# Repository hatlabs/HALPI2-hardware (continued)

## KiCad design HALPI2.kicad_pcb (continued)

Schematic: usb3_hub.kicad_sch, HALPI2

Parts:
C82, C83, C92, C93, C94, C95, C96, C97, C98, C99, C100, C102, C103, C104, C105, C106, C107, C108, C109, C110, C112: 100nF; C_0201_0603Metric; LCSC C76934
C84, C90, C91: 4.7uF; C_0603_1608Metric; LCSC C19666
C85: 22uF; C_1206_3216Metric; LCSC C12891
C86, C111: 10uF; C_0805_2012Metric; LCSC C15850
C87, C88: 12pF; C_0402_1005Metric; LCSC C1547
C89, C101, C113, C114, C115, C116, C117, C118, C119, C120: 1uF; C_0402_1005Metric; LCSC C52923
D23: 1N4148WT; D_SOD-523; LCSC C7420320
FB4: BLM21PG600SN1; L_0805_2012Metric; LCSC C18305
L5: 4.7uH; L_1008_2520Metric; LCSC C19267877
NT1: NetTie_2; NetTie-2_SMD_Pad0.2mm
Q8: QS6M4; SOT-23-6; LCSC C509914
R68, R69, R70, R71, R72, R73, R74, R75, R76, R77, R78, R79, R80, R81, R82: 10k; R_0402_1005Metric; LCSC C25744
R83: 68R; R_0603_1608Metric; LCSC C27592
R84: 56R; R_0603_1608Metric; LCSC C25196
R85: 470k; R_0402_1005Metric; LCSC C25790
R86: 1.6k; R_0402_1005Metric; LCSC C4908
R87: 680R; R_0402_1005Metric; LCSC C25130
R88: 15k; R_0402_1005Metric; LCSC C25756
TP43, TP44: TestPoint; TestPoint_Pad_D1.0mm
U32: UPD720210K8-BAF-A; QFN-76-1EP_9x9mm_P0.4mm_EP3.8x3.8mm; LCSC C2982859
Y2: 24MHz; Crystal_SMD_3225-4Pin_3.2x2.5mm; LCSC C7294566

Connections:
+1.05V: C85.1, C92.1, C93.1, C97.1, C99.1, C102.1, C104.1, C106.1, C108.1, C110.1, C112.1, C114.1, C116.1, C118.1, C119.1, C120.1, L5.1, NT1.1, TP44.1 (1_1), U32.5 (VDD10), U32.11 (VDD10), U32.14 (VDD10), U32.22 (VDD10), U32.28 (VDD10), U32.31 (VDD10), U32.47 (VDD10), U32.64 (VDD10), U32.67 (VDD10), U32.70 (VDD10)
+3.3V: C94.1, C96.1, C98.1, C100.1, C103.1, C105.1, C107.1, C109.1, C111.1, C113.1, C115.1, C117.1, D23.1 (K), FB4.2, R68.1, R69.1, R70.1, R71.2, R72.1, R74.1, R75.1, R77.2, R78.1, R79.2, R80.1, R81.2, R82.2, U32.8 (VDD33), U32.17 (VDD33), U32.25 (VDD33), U32.34 (VDD33), U32.42 (VDD33), U32.50 (AVDD33R), U32.61 (VDD33), U32.76 (VDD33); also elsewhere on the board
+5V: C84.1, C89.2, C90.1, Q8.4 (S), R83.1, U32.49 (V50IN); also elsewhere on the board
/USB3-1.D+: U32.62 (U2DPU); also elsewhere on the board
/USB3-1.D-: U32.63 (U2DNU); also elsewhere on the board
/USB3-1.RX+: C82.1; also elsewhere on the board
/USB3-1.RX-: C83.1; also elsewhere on the board
/USB3-1.TX+: U32.69 (U3RXDPU); also elsewhere on the board
/USB3-1.TX-: U32.68 (U3RXDNU); also elsewhere on the board
/USB3/USB3 Hub/AVDD33: C95.1, C101.1, FB4.1, U32.71 (AVDD33)
/USB3/USB3 Hub/BUSSEL: R71.1, U32.44 (BUSSEL)
/USB3/USB3 Hub/ILIM: R85.2, U32.53 (ILIM)
/USB3/USB3 Hub/LED1B: R82.1, U32.37 (LED1B/SUSPEND)
/USB3/USB3 Hub/NGDRV: Q8.2 (G), U32.52 (NGDRV)
/USB3/USB3 Hub/OCI1B: R69.2, U32.45 (OCI1B); also elsewhere on the board
/USB3/USB3 Hub/OCI2B: R72.2, U32.55 (OCI2B); also elsewhere on the board
/USB3/USB3 Hub/OCI3B: R78.2, U32.57 (OCI3B); also elsewhere on the board
/USB3/USB3 Hub/OCI4B: R80.2, U32.59 (OCI4B)
/USB3/USB3 Hub/PGATE: Q8.5 (G), R83.2, R84.1
/USB3/USB3 Hub/PGDRV: R84.2, U32.51 (PGDRV)
/USB3/USB3 Hub/PPON1B: R74.2, U32.46 (PPON1B/NRDRSTB); also elsewhere on the board
/USB3/USB3 Hub/PPON2B: R75.2, U32.56 (PPON2B); also elsewhere on the board
/USB3/USB3 Hub/PPON3B: R70.2, U32.58 (PPON3B); also elsewhere on the board
/USB3/USB3 Hub/PPON4B: R73.2, U32.60 (PPON4B)
/USB3/USB3 Hub/RESETB: C86.1, D23.2 (A), R68.2, U32.2 (RESETB)
/USB3/USB3 Hub/RREF: R86.2, U32.72 (RREF)
/USB3/USB3 Hub/SPICSB: R76.1, U32.38 (SPICSB)
/USB3/USB3 Hub/SPISCK: R77.1, U32.41 (SPISCK/LED4B)
/USB3/USB3 Hub/SPISI: R79.1, U32.39 (SPISI/LED2B)
/USB3/USB3 Hub/SPISO: R81.1, U32.40 (SPISO/LED3B)
/USB3/USB3 Hub/SW: L5.2, Q8.3 (D), Q8.6 (D), R85.1
/USB3/USB3 Hub/U3TXD+: C82.2, U32.66 (U3TXDPU)
/USB3/USB3 Hub/U3TXD-: C83.2, U32.65 (U3TXDNU)
/USB3/USB3 Hub/U31.D+: U32.9 (U2DP1); also elsewhere on the board
/USB3/USB3 Hub/U31.D-: U32.10 (U2DN1); also elsewhere on the board
/USB3/USB3 Hub/U31.RX+: U32.6 (U3RXDP1); also elsewhere on the board
/USB3/USB3 Hub/U31.RX-: U32.7 (U3RXDN1); also elsewhere on the board
/USB3/USB3 Hub/U31.TX+: U32.3 (U3TXDP1); also elsewhere on the board
/USB3/USB3 Hub/U31.TX-: U32.4 (U3TXDN1); also elsewhere on the board
/USB3/USB3 Hub/U32.D+: U32.18 (U2DP2); also elsewhere on the board
/USB3/USB3 Hub/U32.D-: U32.19 (U2DN2); also elsewhere on the board
/USB3/USB3 Hub/U32.RX+: U32.15 (U3RXDP2); also elsewhere on the board
/USB3/USB3 Hub/U32.RX-: U32.16 (U3RXDN2); also elsewhere on the board
/USB3/USB3 Hub/U32.TX+: U32.12 (U3TXDP2); also elsewhere on the board
/USB3/USB3 Hub/U32.TX-: U32.13 (U3TXDN2); also elsewhere on the board
/USB3/USB3 Hub/U33.D+: U32.26 (U2DP3); also elsewhere on the board
/USB3/USB3 Hub/U33.D-: U32.27 (U2DN3); also elsewhere on the board
/USB3/USB3 Hub/U33.RX+: U32.23 (U3RXDP3); also elsewhere on the board
/USB3/USB3 Hub/U33.RX-: U32.24 (U3RXDN3); also elsewhere on the board
/USB3/USB3 Hub/U33.TX+: U32.20 (U3TXDP3); also elsewhere on the board
/USB3/USB3 Hub/U33.TX-: U32.21 (U3TXDN3); also elsewhere on the board
/USB3/USB3 Hub/V10FB: NT1.2, U32.54 (V10FB)
/USB3/USB3 Hub/V33OUT: C91.1, R88.1, U32.48 (V33OUT)
/USB3/USB3 Hub/XT1: C87.1, U32.74 (XT1), Y2.1
/USB3/USB3 Hub/XT2: R87.1, U32.75 (XT2)
/VBUS_EN: TP43.1 (1_1), U32.43 (VBUSM); also elsewhere on the board
GND: C84.2, C85.2, C86.2, C87.2, C88.2, C89.1, C90.2, C91.2, C92.2, C93.2, C94.2, C95.2, C96.2, C97.2, C98.2, C99.2, C100.2, C101.2, C102.2, C103.2, C104.2, C105.2, C106.2, C107.2, C108.2, C109.2, C110.2, C111.2, C112.2, C113.2, C114.2, C115.2, C116.2, C117.2, C118.2, C119.2, C120.2, Q8.1 (S), R73.1, R76.2, R86.1, R88.2, U32.73 (C(L)), U32.77 (GND), Y2.2, Y2.4; also elsewhere on the board
unnamed: C88.1, R87.2, Y2.3

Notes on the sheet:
Battery charging modes disabled
Three ports are in use
All ports are removable
PPON1B pin function: Port Power Control
Bypass caps
Power Mode: Self-powered
Clock
Reset pin bootstrapping
Individual port power control mode
Downstream ports
Internal switching regulator
AVDD33R
USB3 allows diff pair polarity reversal for data lanes. USB2 pairs need to maintain polarity.
Bootstrapping settings
No external ROM

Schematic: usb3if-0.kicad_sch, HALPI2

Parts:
C80: 10uF; C_0805_2012Metric; LCSC C15850
C81: 220uF; CP_Elec_6.3x7.7; LCSC C5246526
D22: BAT54C,215; SOT-23; LCSC C37704
FB3: BLM21PG600SN1; L_0805_2012Metric; LCSC C18305
J21: USB3_A; USB3.0-A-SMD_916-862A205EY10200; LCSC C2763055
R66: 100k; R_0402_1005Metric; LCSC C25741
R67: 27k; R_0402_1005Metric; LCSC C25771
TP39, TP40, TP41, TP42: TestPoint; TestPoint_Pad_D1.0mm
U29: AP22652W6-7; SOT-23-6; LCSC C2158038
U30, U31: RCLAMP0524P; Diodes_UDFN-10_1.0x2.5mm_P0.5mm; LCSC C907837

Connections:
+5V: C80.1, U29.1 (IN); also elsewhere on the board
/DIS_USB0: D22.2, TP39.1 (1_1); also elsewhere on the board
/USB3-0.D+: J21.3 (D+), U31.2, U31.9; also elsewhere on the board
/USB3-0.D-: J21.2 (D-), U31.1, U31.10; also elsewhere on the board
/USB3-0.RX+: J21.6 (SSRX+), U31.5, U31.6; also elsewhere on the board
/USB3-0.RX-: J21.5 (SSRX-), U31.4, U31.7; also elsewhere on the board
/USB3-0.TX+: J21.9 (SSTX+), U30.4, U30.7; also elsewhere on the board
/USB3-0.TX-: J21.8 (SSTX-), U30.5, U30.6; also elsewhere on the board
/USB3/USB3 Interface/ILIM: R67.2, U29.5 (ILIM)
/USB3/USB3 Interface/VBUS: FB3.2, J21.1 (VBUS), U30.1, U30.10
/USB3/USB3 Interface/VBUS_: C81.1, FB3.1, TP42.1 (1_1), U29.6 (OUT)
/USB3/USB3 Interface/~ENAND: D22.3, R66.1, TP41.1 (1_1), U29.3 (~EN)
/USB3/USB3 Interface/~OC: U29.4 (~FAULT)
/USB3/~EN: D22.1, TP40.1 (1_1); also elsewhere on the board
GND: C80.2, C81.2, J21.4 (GND), J21.7 (DRAIN), J21.10 (SHIELD), R66.2, R67.1, U29.2 (GND), U30.3 (VSS), U30.8 (VSS), U31.3 (VSS), U31.8 (VSS); also elsewhere on the board
unnamed: U30.2, U30.9

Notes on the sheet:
Set current limit to 0.93A
Pull DIS up to disable current limit switch regardless of ~{EN} state
Current Limit switch

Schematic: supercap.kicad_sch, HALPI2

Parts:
C14: 1uF; C_0603_1608Metric; LCSC C15849
TP7: TestPoint; TestPoint_THTPad_D2.0mm_Drill1.0mm
U2: LMV324; SOIC-14_3.9x8.7mm_P1.27mm; LCSC C2837469

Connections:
/Power/Supercaps/Supercap stage2/B+x: U2.3 (+); also elsewhere on the board
/Power/Supercaps/Supercap stage2/B-x: U2.2 (-); also elsewhere on the board
/Power/Supercaps/Supercap stage2/Bo: U2.1; also elsewhere on the board
/Power/Supercaps/Supercap stage3/B+x: U2.12 (+); also elsewhere on the board
/Power/Supercaps/Supercap stage3/B-x: U2.13 (-); also elsewhere on the board
/Power/Supercaps/Supercap stage3/Bo: U2.14; also elsewhere on the board
/Power/Supercaps/Supercap stage4/B+x: U2.10 (+); also elsewhere on the board
/Power/Supercaps/Supercap stage4/B-x: U2.9 (-); also elsewhere on the board
/Power/Supercaps/Supercap stage4/Bo: U2.8; also elsewhere on the board
/Power/VscapE: C14.1, U2.4 (V+); also elsewhere on the board
/Vscap: TP7.1 (1_1); also elsewhere on the board
GND: C14.2, U2.11 (V-); also elsewhere on the board

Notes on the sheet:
Supercapacitor balancing circuit modeled after https://www.eevblog.com/forum/renewable-energy/supercapacitor-balancer/

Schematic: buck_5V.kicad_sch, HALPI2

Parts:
C22: 10uF; C_1206_3216Metric; LCSC C13585
C23, C24, C26: 1uF; C_0402_1005Metric; LCSC C52923
C25: 100nF; C_0603_1608Metric; LCSC C14663
C27: 10uF; C_0805_2012Metric; LCSC C15850
C28: 220uF/16V; CP_Elec_6.3x7.7; LCSC C5246526
C29: 33pF; C_0402_1005Metric; LCSC C1562
J3: 5V Header; PinHeader_2x02_P2.54mm_Vertical; LCSC C7501273; not fitted
L3: APH0630T2R2M; L_Chilisin_BMRx00060630; LCSC C5349701
R26: 100k; R_0402_1005Metric; LCSC C25741
R27: 1k; R_0402_1005Metric; LCSC C11702
R28: 220k; R_0603_1608Metric; LCSC C22961
R29: 30k; R_0603_1608Metric; LCSC C22984
TP20: FB3; TestPoint_Pad_D1.0mm
U6: TPS566238PRQFR; RQF0009A; LCSC C2876603

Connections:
+5V: C26.1, C27.1, C28.1, C29.1, J3.2, J3.4, L3.2, R28.1; also elsewhere on the board
/EN5V: R26.1, U6.3 (EN); also elsewhere on the board
/PG_5V: R27.2; also elsewhere on the board
/Power/Buck converter 5V/BST: C25.2, U6.7 (BST)
/Power/Buck converter 5V/FB: C29.2, R28.2, R29.1, TP20.1 (1_1), U6.2 (FB)
/Power/Buck converter 5V/SW: C25.1, L3.1, U6.8 (SW)
/Power/Buck converter 5V/VCC: C24.1, U6.1 (VCC)
/Vscap: C22.1, C23.1, U6.5 (VIN), U6.6 (VIN); also elsewhere on the board
GND: C22.2, C23.2, C24.2, C26.2, C27.2, C28.2, J3.1, J3.3, R26.2, R29.2, U6.4 (PGND); also elsewhere on the board
unnamed: R27.1, U6.9 (PG)

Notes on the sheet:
FB voltage divider designed to have a 5.1V voltage at Vout
Vin at max. 10.0V
f_{sw} = 600 kHz
Buck converter dropping the supercap voltage down to 5V for the CM4/5 module input and USBs

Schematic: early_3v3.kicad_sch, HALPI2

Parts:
C53: 1uF/50V; C_0603_1608Metric; LCSC C15849
C54: 1uF; C_0603_1608Metric; LCSC C15849
D12, D44, D45: 1N5819WS; D_SOD-323; LCSC C191023
D13: 1N4148WT; D_SOD-523; LCSC C7420320
TP33: TestPoint; TestPoint_Pad_D1.0mm
U10: SE8633K2-HF; SOT-89-3; LCSC C496614

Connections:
+3.3V: D12.2 (A); also elsewhere on the board
+3.3VE: D12.1 (K), D13.1 (K); also elsewhere on the board
/Power/B1_VIN: C53.1, U10.2 (IN); also elsewhere on the board
/Power/Early 3.3V/LDO_OUT: C54.1, D13.2 (A), D44.2 (A), TP33.1 (1_1), U10.3 (OUT)
/Power/VscapE: D44.1 (K), D45.1 (K); also elsewhere on the board
/Vscap: D45.2 (A); also elsewhere on the board
GND: C53.2, C54.2, U10.1 (GND); also elsewhere on the board

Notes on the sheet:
VscapE is used to ensure the supercap balancing circuit op-amps are powered immediately. During undervoltage, TTL op-amps may be at a high state, causing all balancing NPNs to conduct before voltage is increased.
This LDO is required for circuits that need to be powered before the stage 2 buck converters are online (basically, just the current limiter opamp).

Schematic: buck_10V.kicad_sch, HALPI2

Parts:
J2: PoE HAT Vout; PinSocket_2x02_P2.54mm_Vertical; LCSC C2977590
R5: 10m; R_1206_3216Metric; LCSC C105362

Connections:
/Power/B1_VIN: R5.1; also elsewhere on the board
/Power/Buck converter 10V/Vin: J2.2, J2.4, R5.2; also elsewhere on the board
GND: J2.1, J2.3; also elsewhere on the board

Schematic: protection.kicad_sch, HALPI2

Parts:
C1: 100nF/100V; C_0805_2012Metric; LCSC C28233
C2: 1uF; C_0603_1608Metric; LCSC C15849
C3, C4, C5, C6, C8: 1uF/50V; C_0603_1608Metric; LCSC C15849
C7, C9, C10, C11, C12, C13: 10uF/50V; C_1206_3216Metric; LCSC C13585
C38: 1nF; C_0402_1005Metric; LCSC C1523
D1: SMBJ58A; D_SMB; LCSC C41376102
D2: SMBJ28A; D_SMB; LCSC C19077582
D3: MM1Z62; D_SOD-123; LCSC C22395540
D4: 1N4148WS; D_SOD-323_HandSoldering; LCSC C2128
F1, F6: 0451005.MRL; Fuse_Littelfuse-NANO2-451_453; LCSC C48467
FB1, FB2: HCB3216KF-121T60; R_1206_3216Metric; LCSC C357013
L1: FXL0420-1R5-M; L_MWSA0402; LCSC C167205
L2: PCAQ7060MW-102; FILTER-SMD_4P-L7.0-W6.0-TL-A; LCSC C2915648
Q1: WSD46N10DN56; DFN5x6-8L; LCSC C5185328
R1: 10k; R_1206_3216Metric; LCSC C17902
R2: 100k; R_0603_1608Metric; LCSC C25803
R3: 3.3k; R_0603_1608Metric; LCSC C22978
R4: 0.1R; R_1206_3216Metric; LCSC C25334
R34: 200k; R_0603_1608Metric; LCSC C25811
R37: 18k; R_0603_1608Metric; LCSC C25810
TP1: TestPoint; TestPoint_Pad_1.5x1.5mm
TP2, TP3, TP4, TP5, TP6, TP22: TestPoint; TestPoint_Pad_D1.0mm
U1: LM74800; WSON-12-1EP_3x3mm_P0.5mm_EP1.5x2.5mm; LCSC C3215600

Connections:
/Power/Buck converter 10V/Vin: C12.1, C13.1, L1.2; also elsewhere on the board
/Power/Input Protection/CAP: C3.2, U1.11 (CAP)
/Power/Input Protection/DG: Q1.4 (G), U1.1 (DGATE)
/Power/Input Protection/GND_FB: C5.2, C6.2, C8.2, C10.2, FB2.2, L2.1
/Power/Input Protection/HG: Q1.2 (G), U1.8 (HGATE)
/Power/Input Protection/OV: R2.2, R3.1, U1.5 (OV)
/Power/Input Protection/Rdh: C12.2, C13.2, R4.1
/Power/Input Protection/TVS_A: D1.2 (A), D2.2 (A)
/Power/Input Protection/VIN_OVP: C4.1, D4.2 (A), Q1.1 (S), Q1.3 (S), R34.1, TP4.1 (1_1), U1.2 (A), U1.9 (OUT)
/Power/Input Protection/VS: C2.1, C3.1, D3.1 (K), D4.1 (K), R1.2, TP2.1 (1_1), U1.3 (VSNS), U1.4 (SW), U1.6 (EN/UVLO), U1.10 (VS)
/Power/Input Protection/Vin_CM: C7.1, C9.1, C11.1, L1.1, L2.3, TP5.1 (1_1)
/Power/Input Protection/Vin_FB: C5.1, C6.1, C8.1, C10.1, FB1.2, L2.2, TP6.1 (1_1)
/Power/Input Protection/Vin_RPP: FB1.1, Q1.5 (D), U1.12 (C)
/Power/Input Protection/Vin_fused: C1.1, D1.1 (K), F1.1, Q1.6 (D), R1.1, R2.1, TP3.1 (1_1)
/Power/Vin: F1.2; also elsewhere on the board
/VinS: C38.1, R34.2, R37.1, TP22.1 (1_1); also elsewhere on the board
GND: C7.2, C9.2, C11.2, L2.4, R4.2; also elsewhere on the board
GNDPWR: F6.2; also elsewhere on the board
GND_F: C1.2, C2.2, C4.2, C38.2, D2.1 (K), D3.2 (A), F6.1, FB2.1, R3.2, R37.2, TP1.1 (1_1), U1.7 (GND)

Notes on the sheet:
Reverse polarity and reverse current protection
EMI pre-filter design taken from PMP15013 & 62AN101E.
Overvoltage disconnect at 38.6V
Differential EMI filter
Common-mode EMI filter
Overvoltage limit 38.6V
VinS scaled to provide 3.3V for 40V input
Overvoltage and overcurrent protection
Scale Vin down to ADC input

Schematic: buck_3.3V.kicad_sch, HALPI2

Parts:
C30: 10uF; C_1206_3216Metric; LCSC C13585
C31, C32, C34: 1uF; C_0402_1005Metric; LCSC C52923
C33: 100nF; C_0603_1608Metric; LCSC C14663
C35: 10uF; C_0805_2012Metric; LCSC C15850
C36: 220uF/16V; CP_Elec_6.3x7.7; LCSC C5246526
C37: 33pF; C_0402_1005Metric; LCSC C1562
D42: BZT52C4V7S; D_SOD-323; LCSC C19077439
J4: 3.3V Header; PinHeader_2x02_P2.54mm_Vertical; LCSC C7501273; not fitted
L4: APH0630T2R2M; L_Chilisin_BMRx00060630; LCSC C5349701
Q3: YJQ1216A; DFN2020-6L; LCSC C919545
R30: 100k; R_0603_1608Metric; LCSC C25803
R31: 22k; R_0603_1608Metric; LCSC C31850
R121: 4.7k; R_0402_1005Metric; LCSC C25900
R122: 1k; R_0402_1005Metric; LCSC C11702
R137: 130k; R_0603_1608Metric; LCSC C22795
R138: 47k; R_0603_1608Metric; LCSC C25819
TP21, TP65, TP93: FB3; TestPoint_Pad_D1.0mm
U7: TPS566238PRQFR; RQF0009A; LCSC C2876603

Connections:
+3.3V: J4.2, J4.4, Q3.1 (D); also elsewhere on the board
+3.3VP: C34.1, C35.1, C36.1, C37.1, L4.2, Q3.3 (S), R30.1, R121.1, TP65.1 (1_1); also elsewhere on the board
/EN3V3BUCK: D42.1 (K), R137.2, R138.1, U7.3 (EN); also elsewhere on the board
/Power/Buck converter 3.3V/3G: Q3.2 (G), R122.1, TP93.1 (1_1)
/Power/Buck converter 3.3V/BST: C33.2, U7.7 (BST)
/Power/Buck converter 3.3V/FB: C37.2, R30.2, R31.1, TP21.1 (1_1), U7.2 (FB)
/Power/Buck converter 3.3V/SW: C33.1, L4.1, U7.8 (SW)
/Power/Buck converter 3.3V/VCC: C32.1, U7.1 (VCC)
/Vscap: C30.1, C31.1, R137.1, U7.5 (VIN), U7.6 (VIN); also elsewhere on the board
/~EN3V3OUT: R121.2, R122.2; also elsewhere on the board
GND: C30.2, C31.2, C32.2, C34.2, C35.2, C36.2, D42.2 (A), J4.1, J4.3, R31.2, R138.2, U7.4 (PGND); also elsewhere on the board

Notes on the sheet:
FB voltage divider designed to have a 3.33V voltage at Vout
UVLO at 4.5V
Vin at max. 10.3V
Buck converter for the 3.3V rail
f_{sw} = 600 kHz

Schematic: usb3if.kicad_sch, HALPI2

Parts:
C121: 10uF; C_0805_2012Metric; LCSC C15850
C122: 220uF; CP_Elec_6.3x7.7; LCSC C5246526
C123, C124: 100nF; C_0201_0603Metric; LCSC C76934
D24: BAT54C,215; SOT-23; LCSC C37704
FB5: BLM21PG600SN1; L_0805_2012Metric; LCSC C18305
J22: USB3_A; USB3.0-A-SMD_916-862A205EY10200; LCSC C2763055
R89: 100k; R_0402_1005Metric; LCSC C25741
R90: 27k; R_0402_1005Metric; LCSC C25771
TP45, TP46, TP47, TP48: TestPoint; TestPoint_Pad_D1.0mm
U33: AP22652W6-7; SOT-23-6; LCSC C2158038
U34, U35: RCLAMP0524P; Diodes_UDFN-10_1.0x2.5mm_P0.5mm; LCSC C907837

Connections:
+5V: C121.1, U33.1 (IN); also elsewhere on the board
/DIS_USB1: D24.2, TP45.1 (1_1); also elsewhere on the board
/USB3/USB3 Hub/OCI1B: U33.4 (~FAULT); also elsewhere on the board
/USB3/USB3 Hub/PPON1B: D24.1, TP46.1 (1_1); also elsewhere on the board
/USB3/USB3 Hub/U31.D+: J22.3 (D+), U35.2, U35.9; also elsewhere on the board
/USB3/USB3 Hub/U31.D-: J22.2 (D-), U35.1, U35.10; also elsewhere on the board
/USB3/USB3 Hub/U31.RX+: J22.6 (SSRX+), U35.5, U35.6; also elsewhere on the board
/USB3/USB3 Hub/U31.RX-: J22.5 (SSRX-), U35.4, U35.7; also elsewhere on the board
/USB3/USB3 Hub/U31.TX+: C124.1; also elsewhere on the board
/USB3/USB3 Hub/U31.TX-: C123.1; also elsewhere on the board
/USB3/USB3 Hub/USB3 Interface1/ILIM: R90.2, U33.5 (ILIM)
/USB3/USB3 Hub/USB3 Interface1/SSTX+: C124.2, J22.9 (SSTX+), U34.4, U34.7
/USB3/USB3 Hub/USB3 Interface1/SSTX-: C123.2, J22.8 (SSTX-), U34.5, U34.6
/USB3/USB3 Hub/USB3 Interface1/VBUS: FB5.2, J22.1 (VBUS), U34.1, U34.10
/USB3/USB3 Hub/USB3 Interface1/VBUS_: C122.1, FB5.1, TP48.1 (1_1), U33.6 (OUT)
/USB3/USB3 Hub/USB3 Interface1/~ENAND: D24.3, R89.1, TP47.1 (1_1), U33.3 (~EN)
GND: C121.2, C122.2, J22.4 (GND), J22.7 (DRAIN), J22.10 (SHIELD), R89.2, R90.1, U33.2 (GND), U34.3 (VSS), U34.8 (VSS), U35.3 (VSS), U35.8 (VSS); also elsewhere on the board
unnamed: U34.2, U34.9

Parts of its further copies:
C125, C129: 10uF; C_0805_2012Metric; LCSC C15850
C126, C130: 220uF; CP_Elec_6.3x7.7; LCSC C5246526
C127, C128, C131, C132: 100nF; C_0201_0603Metric; LCSC C76934
D25, D26: BAT54C,215; SOT-23; LCSC C37704
FB6, FB7: BLM21PG600SN1; L_0805_2012Metric; LCSC C18305
J23, J24: USB3_A; USB3.0-A-SMD_916-862A205EY10200; LCSC C2763055
R91, R93: 100k; R_0402_1005Metric; LCSC C25741
R92, R94: 27k; R_0402_1005Metric; LCSC C25771
TP49, TP50, TP51, TP52, TP53, TP54, TP55, TP56: TestPoint; TestPoint_Pad_D1.0mm
U36, U39: AP22652W6-7; SOT-23-6; LCSC C2158038
U37, U38, U40, U41: RCLAMP0524P; Diodes_UDFN-10_1.0x2.5mm_P0.5mm; LCSC C907837

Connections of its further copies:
+5V: C125.1, C129.1, U36.1 (IN), U39.1 (IN); also elsewhere on the board
/DIS_USB2: D25.2, TP49.1 (1_1); also elsewhere on the board
/DIS_USB3: D26.2, TP53.1 (1_1); also elsewhere on the board
/USB3/USB3 Hub/OCI2B: U36.4 (~FAULT); also elsewhere on the board
/USB3/USB3 Hub/OCI3B: U39.4 (~FAULT); also elsewhere on the board
/USB3/USB3 Hub/PPON2B: D25.1, TP50.1 (1_1); also elsewhere on the board
/USB3/USB3 Hub/PPON3B: D26.1, TP54.1 (1_1); also elsewhere on the board
/USB3/USB3 Hub/U32.D+: J23.3 (D+), U38.2, U38.9; also elsewhere on the board
/USB3/USB3 Hub/U32.D-: J23.2 (D-), U38.1, U38.10; also elsewhere on the board
/USB3/USB3 Hub/U32.RX+: J23.6 (SSRX+), U38.5, U38.6; also elsewhere on the board
/USB3/USB3 Hub/U32.RX-: J23.5 (SSRX-), U38.4, U38.7; also elsewhere on the board
/USB3/USB3 Hub/U32.TX+: C128.1; also elsewhere on the board
/USB3/USB3 Hub/U32.TX-: C127.1; also elsewhere on the board
/USB3/USB3 Hub/U33.D+: J24.3 (D+), U41.2, U41.9; also elsewhere on the board
/USB3/USB3 Hub/U33.D-: J24.2 (D-), U41.1, U41.10; also elsewhere on the board
/USB3/USB3 Hub/U33.RX+: J24.6 (SSRX+), U41.5, U41.6; also elsewhere on the board
/USB3/USB3 Hub/U33.RX-: J24.5 (SSRX-), U41.4, U41.7; also elsewhere on the board
/USB3/USB3 Hub/U33.TX+: C132.1; also elsewhere on the board
/USB3/USB3 Hub/U33.TX-: C131.1; also elsewhere on the board
/USB3/USB3 Hub/USB3 Interface2/ILIM: R92.2, U36.5 (ILIM)
/USB3/USB3 Hub/USB3 Interface2/SSTX+: C128.2, J23.9 (SSTX+), U37.4, U37.7
/USB3/USB3 Hub/USB3 Interface2/SSTX-: C127.2, J23.8 (SSTX-), U37.5, U37.6
/USB3/USB3 Hub/USB3 Interface2/VBUS: FB6.2, J23.1 (VBUS), U37.1, U37.10
/USB3/USB3 Hub/USB3 Interface2/VBUS_: C126.1, FB6.1, TP52.1 (1_1), U36.6 (OUT)
/USB3/USB3 Hub/USB3 Interface2/~ENAND: D25.3, R91.1, TP51.1 (1_1), U36.3 (~EN)
/USB3/USB3 Hub/USB3 Interface3/ILIM: R94.2, U39.5 (ILIM)
/USB3/USB3 Hub/USB3 Interface3/SSTX+: C132.2, J24.9 (SSTX+), U40.4, U40.7
/USB3/USB3 Hub/USB3 Interface3/SSTX-: C131.2, J24.8 (SSTX-), U40.5, U40.6
/USB3/USB3 Hub/USB3 Interface3/VBUS: FB7.2, J24.1 (VBUS), U40.1, U40.10
/USB3/USB3 Hub/USB3 Interface3/VBUS_: C130.1, FB7.1, TP56.1 (1_1), U39.6 (OUT)
/USB3/USB3 Hub/USB3 Interface3/~ENAND: D26.3, R93.1, TP55.1 (1_1), U39.3 (~EN)
GND: C125.2, C126.2, C129.2, C130.2, J23.4 (GND), J23.7 (DRAIN), J23.10 (SHIELD), J24.4 (GND), J24.7 (DRAIN), J24.10 (SHIELD), R91.2, R92.1, R93.2, R94.1, U36.2 (GND), U37.3 (VSS), U37.8 (VSS), U38.3 (VSS), U38.8 (VSS), U39.2 (GND), U40.3 (VSS), U40.8 (VSS), U41.3 (VSS), U41.8 (VSS); also elsewhere on the board
unnamed: U37.2, U37.9
unnamed: U40.2, U40.9

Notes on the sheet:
Set current limit to 0.93A
Pull DIS up to disable current limit switch regardless of ~{EN} state
Current Limit switch

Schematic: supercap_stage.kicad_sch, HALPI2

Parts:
C15: HT-2R7-J256VYJ21; CP_Radial_D16.0mm_P7.50mm; JLCPCB_IGNORE 1
D5: B5819W; D_SOD-123; LCSC C8598
Q13: FMMT617; SOT-23; LCSC C686650
R6: 33k; R_0603_1608Metric; LCSC C4216
R7, R8, R10: 51k; R_0402_1005Metric; LCSC C25794
R9: 49.9k; R_0402_1005Metric; LCSC C25897
R141: 560R; R_0603_1608Metric; LCSC C23204
R145: 20R; R_1210_3225Metric; LCSC C620667
TP8: TestPoint; TestPoint_Pad_D1.0mm
TP9, TP10: TestPoint; TestPoint_Pad_D1.5mm
U2: LMV324; SOIC-14_3.9x8.7mm_P1.27mm; LCSC C2837469

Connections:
/Power/Supercaps/Supercap stage1/B: Q13.1 (B), R141.2
/Power/Supercaps/Supercap stage1/B+x: R7.2, R8.1, U2.5 (+)
/Power/Supercaps/Supercap stage1/B-x: R9.2, R10.1, U2.6 (-)
/Power/Supercaps/Supercap stage1/Bo: R141.1, TP8.1 (1_1), U2.7
/Power/Supercaps/Supercap stage1/C+: C15.1, D5.1 (K), R7.1, R145.1, TP9.1 (1_1); also elsewhere on the board
/Power/Supercaps/Supercap stage1/Qc: Q13.3 (C), R145.2
/Power/Supercaps/Supercap stage1/R+: R6.1, R9.1; also elsewhere on the board
/Power/Supercaps/Supercap stage2/B+x: U2.3 (+); also elsewhere on the board
/Power/Supercaps/Supercap stage2/B-x: U2.2 (-); also elsewhere on the board
/Power/Supercaps/Supercap stage2/Bo: U2.1; also elsewhere on the board
/Power/Supercaps/Supercap stage3/B+x: U2.12 (+); also elsewhere on the board
/Power/Supercaps/Supercap stage3/B-x: U2.13 (-); also elsewhere on the board
/Power/Supercaps/Supercap stage3/Bo: U2.14; also elsewhere on the board
/Power/Supercaps/Supercap stage4/B+x: U2.10 (+); also elsewhere on the board
/Power/Supercaps/Supercap stage4/B-x: U2.9 (-); also elsewhere on the board
/Power/Supercaps/Supercap stage4/Bo: U2.8; also elsewhere on the board
GND: C15.2, D5.2 (A), Q13.2 (E), R6.2, R8.2, R10.2, TP10.1 (1_1); also elsewhere on the board

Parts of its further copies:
C17, C19, C21: HT-2R7-J256VYJ21; CP_Radial_D16.0mm_P7.50mm; JLCPCB_IGNORE 1
D6, D7, D8: B5819W; D_SOD-123; LCSC C8598
Q14, Q15, Q16: FMMT617; SOT-23; LCSC C686650
R11, R16, R21: 33k; R_0603_1608Metric; LCSC C4216
R12, R13, R15, R17, R18, R20, R22, R23, R25: 51k; R_0402_1005Metric; LCSC C25794
R14, R19, R24: 49.9k; R_0402_1005Metric; LCSC C25897
R142, R143, R144: 560R; R_0603_1608Metric; LCSC C23204
R146, R147, R148: 20R; R_1210_3225Metric; LCSC C620667
TP11, TP14, TP17: TestPoint; TestPoint_Pad_D1.0mm
TP12, TP13, TP15, TP16, TP18, TP19: TestPoint; TestPoint_Pad_D1.5mm

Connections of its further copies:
/Power/Supercaps/Supercap stage1/C+: C17.2, D6.2 (A), Q14.2 (E), R15.2, TP13.1 (1_1); also elsewhere on the board
/Power/Supercaps/Supercap stage1/R+: R11.2, R13.2; also elsewhere on the board
/Power/Supercaps/Supercap stage2/B: Q14.1 (B), R142.2
/Power/Supercaps/Supercap stage2/B+x: R12.2, R13.1; also elsewhere on the board
/Power/Supercaps/Supercap stage2/B-x: R14.2, R15.1; also elsewhere on the board
/Power/Supercaps/Supercap stage2/Bo: R142.1, TP11.1 (1_1); also elsewhere on the board
/Power/Supercaps/Supercap stage2/C+: C17.1, C19.2, D6.1 (K), D7.2 (A), Q15.2 (E), R12.1, R20.2, R146.1, TP12.1 (1_1), TP16.1 (1_1)
/Power/Supercaps/Supercap stage2/Qc: Q14.3 (C), R146.2
/Power/Supercaps/Supercap stage2/R+: R11.1, R14.1, R16.2, R18.2
/Power/Supercaps/Supercap stage3/B: Q15.1 (B), R143.2
/Power/Supercaps/Supercap stage3/B+x: R17.2, R18.1; also elsewhere on the board
/Power/Supercaps/Supercap stage3/B-x: R19.2, R20.1; also elsewhere on the board
/Power/Supercaps/Supercap stage3/Bo: R143.1, TP14.1 (1_1); also elsewhere on the board
/Power/Supercaps/Supercap stage3/C+: C19.1, C21.2, D7.1 (K), D8.2 (A), Q16.2 (E), R17.1, R25.2, R147.1, TP15.1 (1_1), TP19.1 (1_1)
/Power/Supercaps/Supercap stage3/Qc: Q15.3 (C), R147.2
/Power/Supercaps/Supercap stage3/R+: R16.1, R19.1, R21.2, R23.2
/Power/Supercaps/Supercap stage4/B: Q16.1 (B), R144.2
/Power/Supercaps/Supercap stage4/B+x: R22.2, R23.1; also elsewhere on the board
/Power/Supercaps/Supercap stage4/B-x: R24.2, R25.1; also elsewhere on the board
/Power/Supercaps/Supercap stage4/Bo: R144.1, TP17.1 (1_1); also elsewhere on the board
/Power/Supercaps/Supercap stage4/Qc: Q16.3 (C), R148.2
/Vscap: C21.1, D8.1 (K), R21.1, R22.1, R24.1, R148.1, TP18.1 (1_1); also elsewhere on the board

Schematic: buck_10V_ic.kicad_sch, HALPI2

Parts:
C170: 47uF/50V; CP_Elec_6.3x7.7; LCSC C44606723
C171: 1uF; C_0402_1005Metric; LCSC C52923
C172: 10uF/50V; C_1206_3216Metric; LCSC C13585
C173, C174: 1uF/50V; C_0603_1608Metric; LCSC C15849
C175: 4.7uF; C_0603_1608Metric; LCSC C19666
C176: 2.2uF; C_0603_1608Metric; LCSC C23630
C177: 100nF; C_0402_1005Metric; LCSC C1525
C178: 3.3nF; C_0603_1608Metric; LCSC C1613
C179: 10nF; C_0603_1608Metric; LCSC C57112
C180: 1nF; C_0603_1608Metric; LCSC C1588; not fitted
C181: 2.2nF; C_0603_1608Metric; LCSC C1604
C182: 1uF; C_0603_1608Metric; LCSC C15849
C183: 220uF/16V; CP_Elec_6.3x7.7; LCSC C5246526
C189: 1nF; C_0603_1608Metric; LCSC C1588
L10: FXL1040-6R8-M; L_Changjiang_FXL1040; LCSC C167231
R120: 130k; R_0603_1608Metric; LCSC C22795
R123: 2k; R_0402_1005Metric; LCSC C4109
R124, R126: 68k; R_0603_1608Metric; LCSC C23231
R125: 3.3R; R_0402_1005Metric; LCSC C25165
R127: 20k; R_0603_1608Metric; LCSC C4184
R128: 0R; R_0603_1608Metric; LCSC C21189; not fitted
R129: 39k; R_0603_1608Metric; LCSC C23153
R130: 3.3k; R_0603_1608Metric; LCSC C22978
TP90: TestPoint; TestPoint_Pad_D1.0mm
TP91: FB1; TestPoint_Pad_D1.0mm
U52: SIC463ED-T1-GE3; QFN_61ED-T1-GE3_VIS; LCSC C3191905

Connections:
/Power/B1_VIN: C170.1, C172.1, C173.1, C174.1, TP90.1 (1_1), U52.1 (VCIN), U52.3 (EN), U52.7 (VIN), U52.8 (VIN), U52.29 (VIN); also elsewhere on the board
/Power/Buck converter 10V/Buck 10V IC/BOOT: C177.1, R125.1
/Power/Buck converter 10V/Buck 10V IC/BOOTx: C177.2, U52.4 (BOOT)
/Power/Buck converter 10V/Buck 10V IC/COMP: C179.1, R126.1
/Power/Buck converter 10V/Buck 10V IC/COMPx: R126.2, U52.21 (COMP)
/Power/Buck converter 10V/Buck 10V IC/ILIM: R124.2, U52.25 (ILIM)
/Power/Buck converter 10V/Buck 10V IC/MODE: R123.2, U52.27 (MODE)
/Power/Buck converter 10V/Buck 10V IC/PHASE: R125.2, U52.5 (PHASE), U52.6 (PHASE)
/Power/Buck converter 10V/Buck 10V IC/SNUB_: C180.1, R128.1
/Power/Buck converter 10V/Buck 10V IC/SS: C176.1, U52.19 (SS)
/Power/Buck converter 10V/Buck 10V IC/SW: L10.1, R127.1, R128.2, U52.12 (SW), U52.13 (SW), U52.14 (SW)
/Power/Buck converter 10V/Buck 10V IC/VDD: C171.1, U52.26 (VDD)
/Power/Buck converter 10V/Buck 10V IC/VDRV: C175.1, U52.16 (VDRV)
/Power/Buck converter 10V/Buck 10V IC/VSNS: C178.1, U52.20 (VSNS)
/Power/Buck converter 10V/Buck 10V IC/VSNSy: C178.2, C181.1, R127.2
/Power/Buck converter 10V/Buck 10V IC/fSW: R120.2, U52.24 (fSW)
/Power/Buck converter 10V/FB: C189.1, R129.2, R130.1, TP91.1 (1_1), U52.22 (VFB); also elsewhere on the board
/Vscap: C181.2, C182.1, C183.1, L10.2, R129.1; also elsewhere on the board
GND: C170.2, C171.2, C172.2, C173.2, C174.2, C175.2, C176.2, C179.2, C180.2, C182.2, C183.2, C189.2, R120.1, R123.1, R124.1, R130.2, U52.9 (PGND), U52.10 (PGND), U52.11 (PGND), U52.17 (PGND), U52.23 (AGND), U52.28 (AGND), U52.30 (PGND); also elsewhere on the board

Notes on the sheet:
NOTE: If the converter is configured with a different SiC46x variant, ILIM must be adjusted as well (even for the same output current value).
f_{sw} = 405 kHz
Power save enabled, internal regulator enabled
FB voltage divider designed to have Vout of 10.25V
Acceptable variants: SiC463ED SiC462ED SiC461ED
Extremely slow soft start
Snubber circuit
First stage buck converter

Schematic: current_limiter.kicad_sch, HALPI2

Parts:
C167, C169, C187: 1uF; C_0402_1005Metric; LCSC C52923
C168: 100nF; C_0603_1608Metric; LCSC C14663
D37: BZX584C3V3; D_SOD-523; LCSC C19077462
D38: 1N4148WT; D_SOD-523; LCSC C7420320
Q10, Q11: MMBT5551; SOT-23; LCSC C2145
Q12: LBSS84LT1G; SOT-23; LCSC C8492
R112: 100k; R_0402_1005Metric; LCSC C25741
R113: 10k; R_0402_1005Metric; LCSC C25744
R114: 510R; R_0402_1005Metric; LCSC C25123
R115: 100R; R_0402_1005Metric; LCSC C25076
R116: 10k; R_0603_1608Metric_Pad0.98x0.95mm_HandSolder; LCSC C25804
R117: 510k; R_0603_1608Metric_Pad0.98x0.95mm_HandSolder; LCSC C23192
R118: 470R; R_0603_1608Metric_Pad0.98x0.95mm_HandSolder; LCSC C23179
R119: 4.7k; R_0603_1608Metric_Pad0.98x0.95mm_HandSolder; LCSC C23162
SW4: MSS12C02LS-HB2.0; SW-SMD_MSS12C02LS-HB2.0-1; LCSC C3008584
TP86, TP87, TP88, TP89, TP92: TestPoint; TestPoint_Pad_D1.0mm
U50: COS1333TR; SOT-23-5; LCSC C693072
U51, U55: LMV321-TR; SOT-23-5; LCSC C362273

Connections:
+3.3VE: C169.2, C187.2, U51.5 (V+), U55.5 (V+); also elsewhere on the board
/Iin: TP92.1 (1_1), U55.3 (-), U55.4; also elsewhere on the board
/Power/B1_VIN: U50.3 (+); also elsewhere on the board
/Power/Buck converter 10V/Current Limiter/CCSB1: Q10.1 (B), R113.2
/Power/Buck converter 10V/Current Limiter/CCSC1: Q10.3 (C), Q11.1 (B), R112.2
/Power/Buck converter 10V/Current Limiter/CCSE2: Q11.2 (E), R113.1, R114.1
/Power/Buck converter 10V/Current Limiter/DA-: Q12.2 (S), R115.2, U50.4 (-)
/Power/Buck converter 10V/Current Limiter/DAO: Q12.1 (G), U50.1
/Power/Buck converter 10V/Current Limiter/FVSS: C167.1, D37.2 (A), Q11.3 (C), TP86.1 (1_1), U50.2 (V-)
/Power/Buck converter 10V/Current Limiter/I2A9: R119.1, SW4.1
/Power/Buck converter 10V/Current Limiter/IinD: Q12.3 (D), R116.1, R117.1, SW4.2, TP87.1 (1_1)
/Power/Buck converter 10V/Current Limiter/Iinf: C168.1, R117.2, TP88.1 (1_1), U51.1 (+), U55.1 (+)
/Power/Buck converter 10V/Current Limiter/VF-: D38.1 (K), R118.1, TP89.1 (1_1), U51.3 (-)
/Power/Buck converter 10V/Current Limiter/VFO: D38.2 (A), U51.4
/Power/Buck converter 10V/FB: R118.2; also elsewhere on the board
/Power/Buck converter 10V/Vin: C167.2, D37.1 (K), R112.1, R115.1, U50.5 (V+); also elsewhere on the board
GND: C168.2, C169.1, C187.1, Q10.2 (E), R114.2, R116.2, R119.2, SW4.SH, U51.2 (V-), U55.2 (V-); also elsewhere on the board

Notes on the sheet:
Switch at 1-2 increases input current limit to 2.5A
R_{CLout}
Floating opamp with current output. Design from LMP8646.
Voltage follower required to provide a low-impedance source for Iin. Otherwise the MCU GPIO default pull-downs affect Vfb.
Voltage follower with diode to prevent the opamp from pulling FB down
Voltage at Iin corresponds to input current
Current limiting circuit
Constant current source with about 1.1mA current through the biasing zener diode
R_{f}
Current limit adjustment
C_{f}
Heavy low-pass filtering required for buck stability.

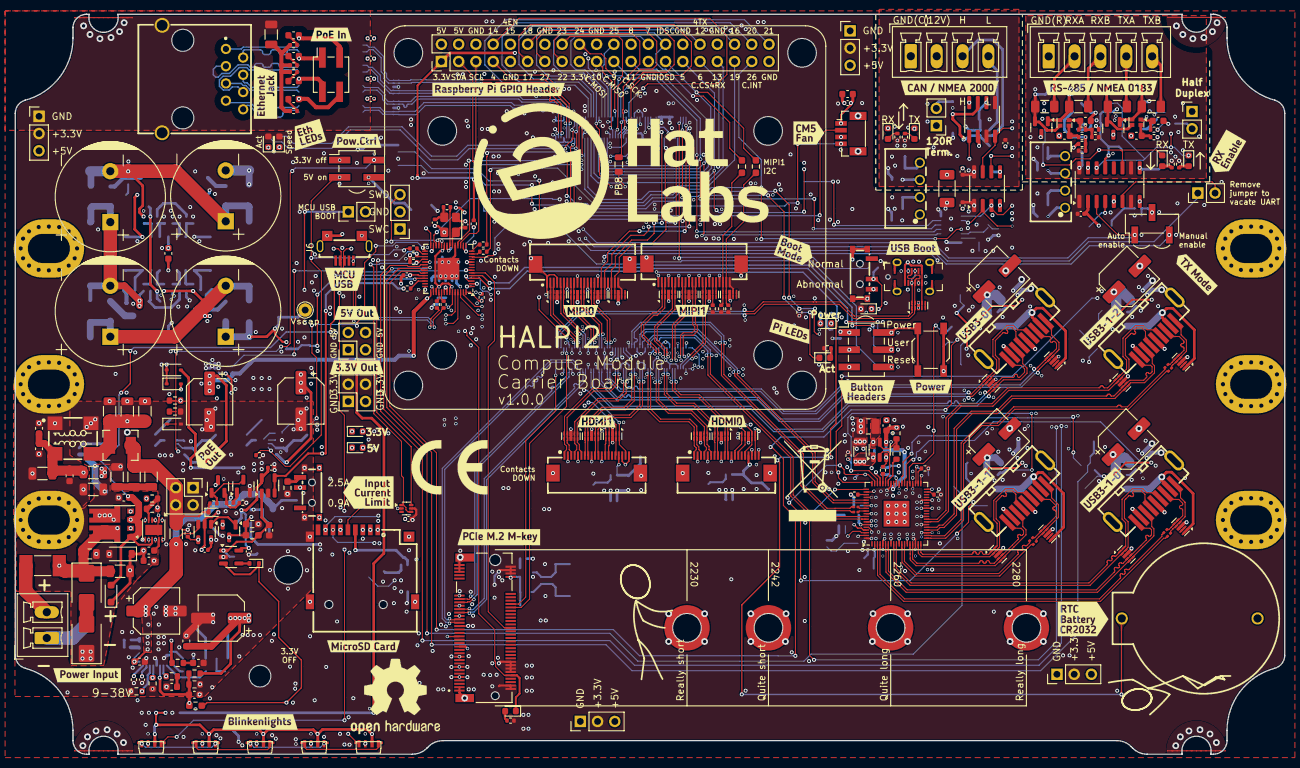
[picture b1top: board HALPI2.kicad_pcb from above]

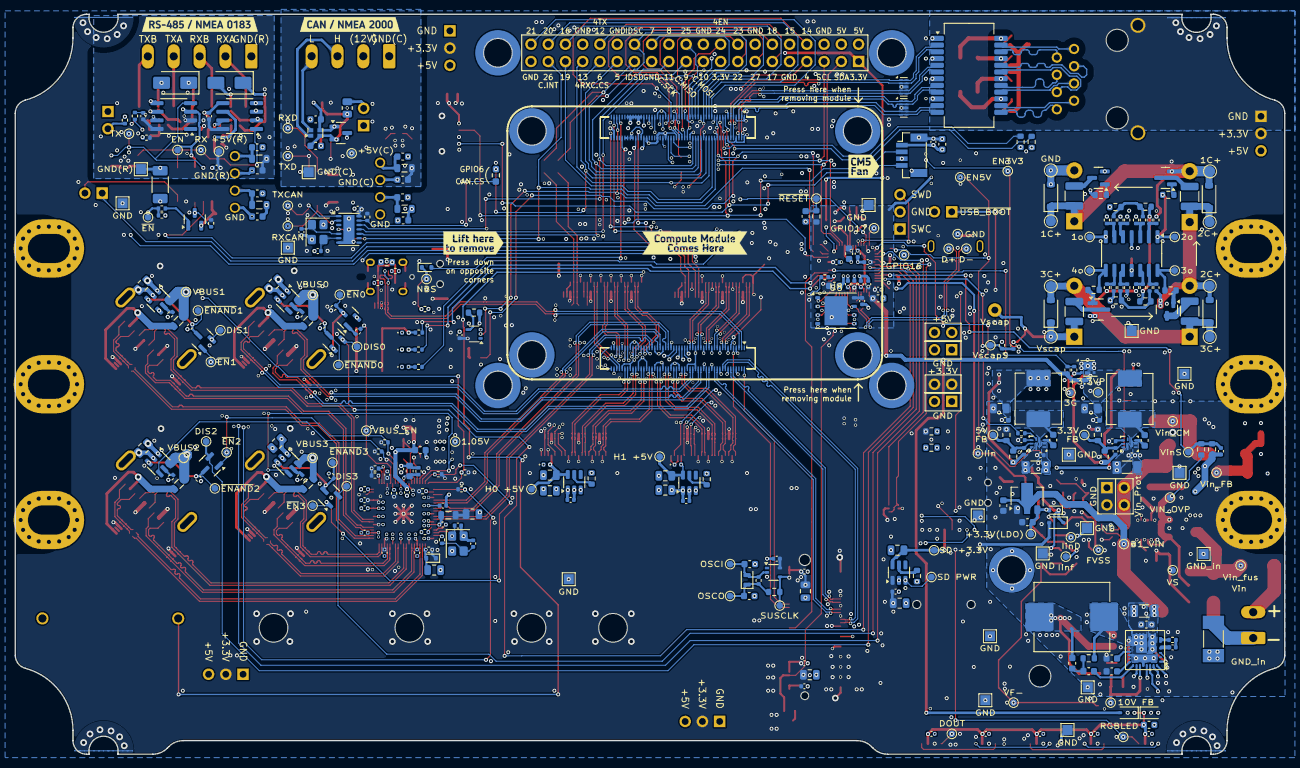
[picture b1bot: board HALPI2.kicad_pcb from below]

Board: 6 copper layers, 187.0 x 109.0 mm, 703 parts (392 on the bottom side), 442 nets.

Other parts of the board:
**REF: MountingHole; MountingHole_3.2mm_M3
kibuzzard-67A4E098: G***; kibuzzard-67A4E098
kibuzzard-67A4EFFF: G***; kibuzzard-67A4EFFF
kibuzzard-67A4F211: G***; kibuzzard-67A4F211
kibuzzard-67A4F495: G***; kibuzzard-67A4F495
kibuzzard-67A5E855: G***; kibuzzard-67A5E855
kibuzzard-67A506CE: G***; kibuzzard-67A506CE
kibuzzard-67A522AF: G***; kibuzzard-67A522AF
kibuzzard-67A522DC: G***; kibuzzard-67A522DC
kibuzzard-67A523D0: G***; kibuzzard-67A523D0
kibuzzard-67A5060E: G***; kibuzzard-67A5060E
kibuzzard-67A50783: G***; kibuzzard-67A50783
kibuzzard-67A50798: G***; kibuzzard-67A50798
kibuzzard-67ADC7EF: G***; kibuzzard-67ADC7EF
kibuzzard-67ADD9EC: G***; kibuzzard-67ADD9EC
kibuzzard-67ADDC90: G***; kibuzzard-67ADDC90
kibuzzard-67B6DB65: G***; kibuzzard-67B6DB65
kibuzzard-67BA0D10: G***; kibuzzard-67BA0D10
kibuzzard-67BB306D: G***; kibuzzard-67BB306D
kibuzzard-67BB324E: G***; kibuzzard-67BB324E
kibuzzard-67BBA1EB: G***; kibuzzard-67BBA1EB
kibuzzard-67BC858D: G***; kibuzzard-67BC858D
kibuzzard-67BC5486: G***; kibuzzard-67BC5486
kibuzzard-67F28842: G***; kibuzzard-67F28842
kibuzzard-67FBB247: G***; kibuzzard-67FBB247
kibuzzard-67FC0F86: G***; kibuzzard-67FC0F86
kibuzzard-67FC0F98: G***; kibuzzard-67FC0F98
kibuzzard-67FCB5D0: G***; kibuzzard-67FCB5D0
kibuzzard-67FCB612: G***; kibuzzard-67FCB612
kibuzzard-68DABA63: G***; kibuzzard-68DABA63
kibuzzard-68DCD35F: G***; kibuzzard-68DCD35F
kibuzzard-68DCD260: G***; kibuzzard-68DCD260
kibuzzard-68DCEE1F: G***; kibuzzard-68DCEE1F
kibuzzard-68DCEEC9: G***; kibuzzard-68DCEEC9
kibuzzard-68DE72DD: G***; kibuzzard-68DE72DD
kibuzzard-689EDF6F: G***; kibuzzard-689EDF6F
kibuzzard-6818A250: G***; kibuzzard-6818A250
kibuzzard-6842BA53: G***; kibuzzard-6842BA53
kibuzzard-6842BA62: G***; kibuzzard-6842BA62
